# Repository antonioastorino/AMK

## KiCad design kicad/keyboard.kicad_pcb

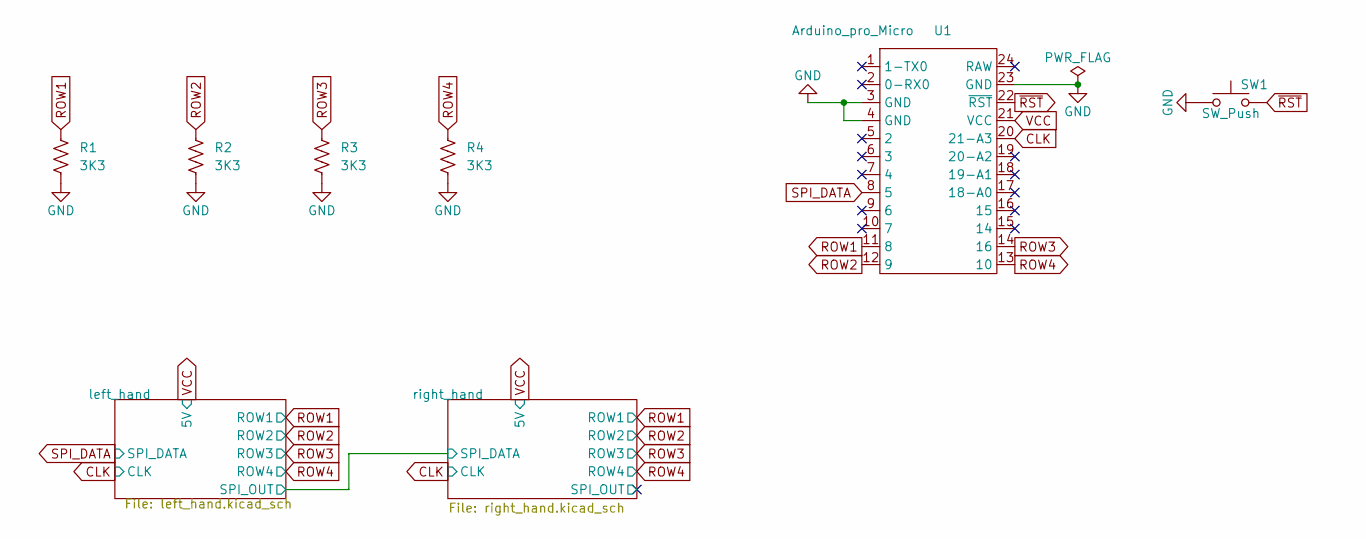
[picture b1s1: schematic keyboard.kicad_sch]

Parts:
R1, R2, R3, R4: 3K3; R_Axial_DIN0207_L6.3mm_D2.5mm_P7.62mm_Horizontal
SW1: SW_Push; DIP-2_P5.08mm
U1: Arduino_pro_Micro; DIP-24_W15.24mm

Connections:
CLK: U1.20 (21-A3); also elsewhere on the board
GND: R1.2, R2.2, R3.2, R4.2, SW1.1, U1.3 (GND), U1.4 (GND), U1.23 (GND); also elsewhere on the board
ROW1: R1.1, U1.11 (8); also elsewhere on the board
ROW2: R2.1, U1.12 (9); also elsewhere on the board
ROW3: R3.1, U1.14 (16); also elsewhere on the board
ROW4: R4.1, U1.13 (10); also elsewhere on the board
SPI_DATA: U1.8 (5); also elsewhere on the board
VCC: U1.21 (VCC); also elsewhere on the board
~RST: SW1.2, U1.22 (~RST)

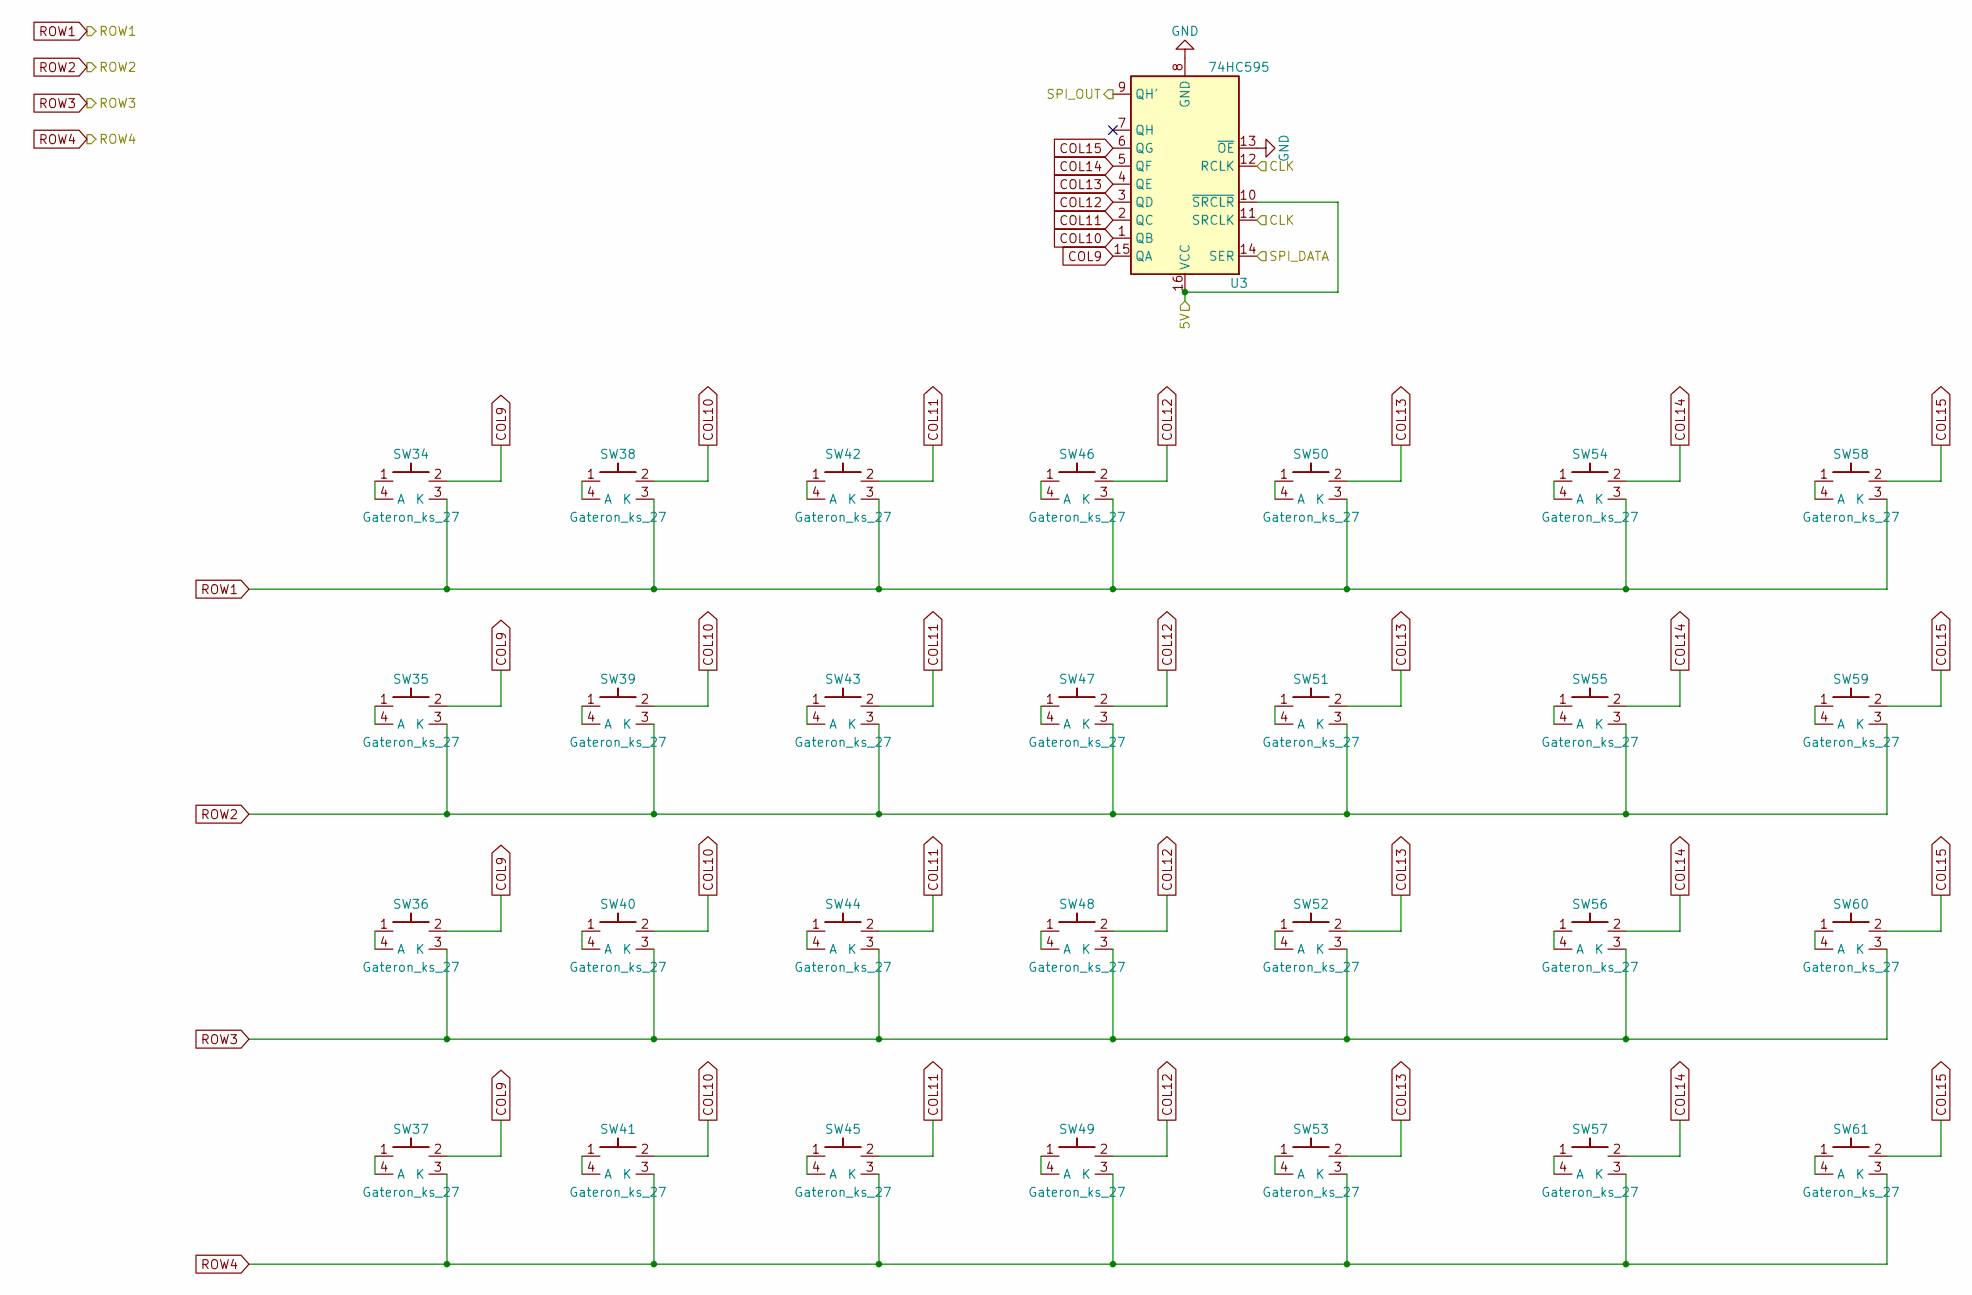
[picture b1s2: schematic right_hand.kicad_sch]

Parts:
SW34, SW35, SW36, SW37, SW38, SW39, SW40, SW41, SW42, SW43, SW44, SW45, SW46, SW47, SW48, SW49, SW50, SW51, SW52, SW53, SW54, SW55, SW56, SW57, SW58, SW59, SW60, SW61: Gateron_ks_27
U3: 74HC595; DIP-16_W7.62mm_Socket

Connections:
/left_hand/SPI_OUT: U3.14 (SER); also elsewhere on the board
/right_hand/SPI_OUT: U3.9 (QH')
CLK: U3.11 (SRCLK), U3.12 (RCLK); also elsewhere on the board
COL9: SW34.2, SW35.2, SW36.2, SW37.2, U3.15 (QA)
COL10: SW38.2, SW39.2, SW40.2, SW41.2, U3.1 (QB)
COL11: SW42.2, SW43.2, SW44.2, SW45.2, U3.2 (QC)
COL12: SW46.2, SW47.2, SW48.2, SW49.2, U3.3 (QD)
COL13: SW50.2, SW51.2, SW52.2, SW53.2, U3.4 (QE)
COL14: SW54.2, SW55.2, SW56.2, SW57.2, U3.5 (QF)
COL15: SW58.2, SW59.2, SW60.2, SW61.2, U3.6 (QG)
GND: U3.8 (GND), U3.13 (~OE); also elsewhere on the board
unnamed: SW34.1, SW34.4 (A)
unnamed: SW35.1, SW35.4 (A)
unnamed: SW36.1, SW36.4 (A)
unnamed: SW37.1, SW37.4 (A)
unnamed: SW38.1, SW38.4 (A)
unnamed: SW39.1, SW39.4 (A)
unnamed: SW40.1, SW40.4 (A)
unnamed: SW41.1, SW41.4 (A)
unnamed: SW42.1, SW42.4 (A)
unnamed: SW43.1, SW43.4 (A)
unnamed: SW44.1, SW44.4 (A)
unnamed: SW45.1, SW45.4 (A)
unnamed: SW46.1, SW46.4 (A)
unnamed: SW47.1, SW47.4 (A)
unnamed: SW48.1, SW48.4 (A)
unnamed: SW49.1, SW49.4 (A)
unnamed: SW50.1, SW50.4 (A)
unnamed: SW51.1, SW51.4 (A)
unnamed: SW52.1, SW52.4 (A)
unnamed: SW53.1, SW53.4 (A)
unnamed: SW54.1, SW54.4 (A)
unnamed: SW55.1, SW55.4 (A)
unnamed: SW56.1, SW56.4 (A)
unnamed: SW57.1, SW57.4 (A)
unnamed: SW58.1, SW58.4 (A)
unnamed: SW59.1, SW59.4 (A)
unnamed: SW60.1, SW60.4 (A)
unnamed: SW61.1, SW61.4 (A)
ROW1: SW34.3 (K), SW38.3 (K), SW42.3 (K), SW46.3 (K), SW50.3 (K), SW54.3 (K), SW58.3 (K); also elsewhere on the board
ROW2: SW35.3 (K), SW39.3 (K), SW43.3 (K), SW47.3 (K), SW51.3 (K), SW55.3 (K), SW59.3 (K); also elsewhere on the board
ROW3: SW36.3 (K), SW40.3 (K), SW44.3 (K), SW48.3 (K), SW52.3 (K), SW56.3 (K), SW60.3 (K); also elsewhere on the board
ROW4: SW37.3 (K), SW41.3 (K), SW45.3 (K), SW49.3 (K), SW53.3 (K), SW57.3 (K), SW61.3 (K); also elsewhere on the board
VCC: U3.10 (~SRCLR), U3.16 (VCC); also elsewhere on the board

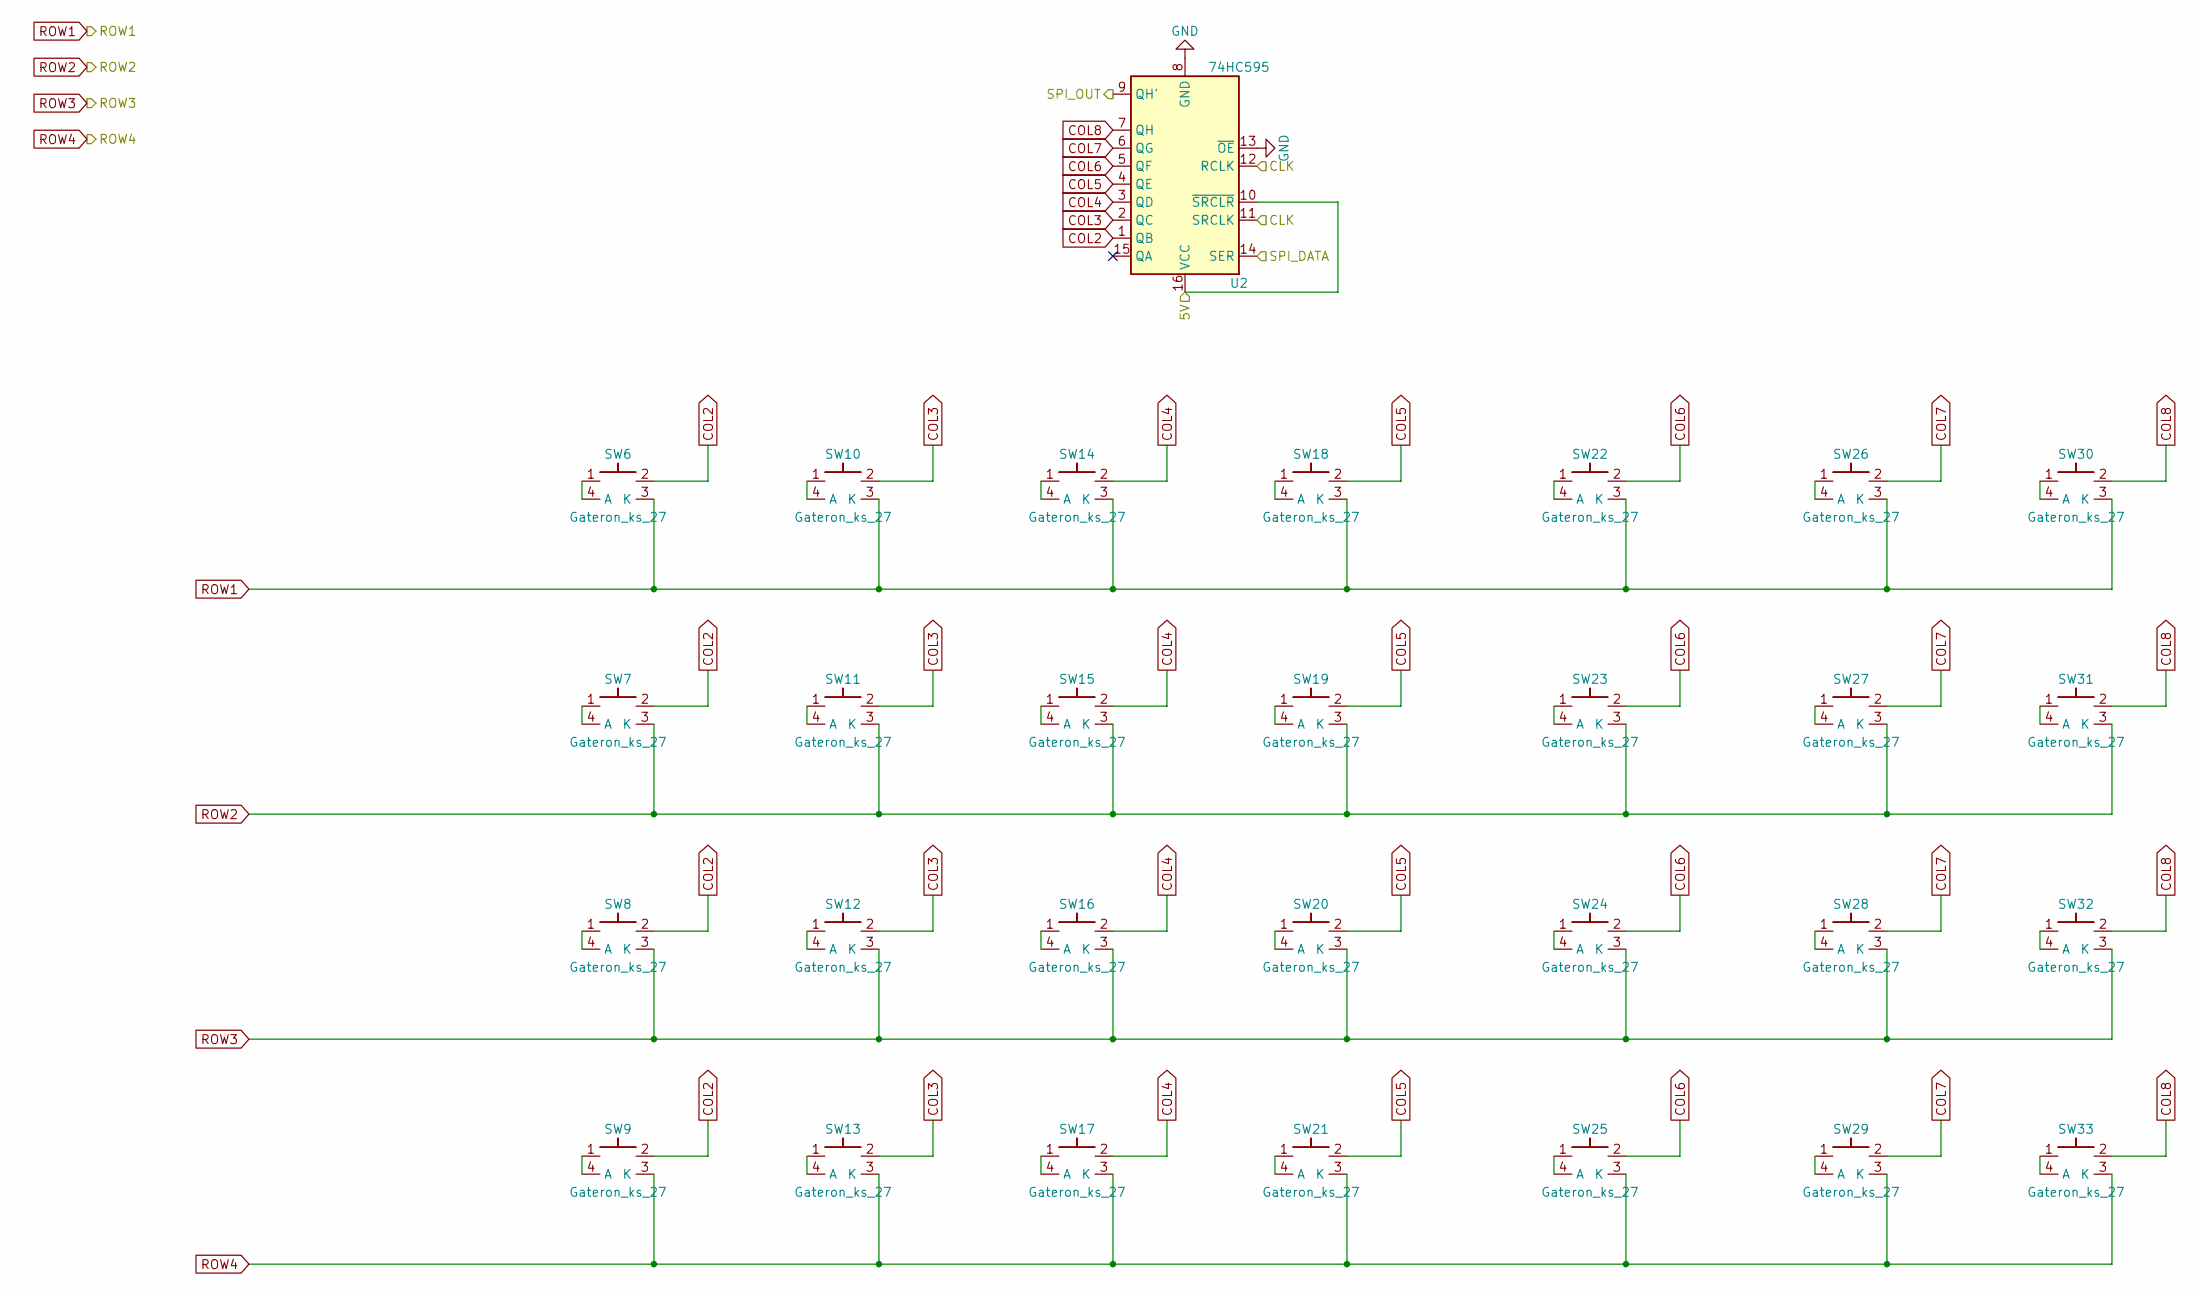
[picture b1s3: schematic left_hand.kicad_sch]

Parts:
SW6, SW7, SW8, SW9, SW10, SW11, SW12, SW13, SW14, SW15, SW16, SW17, SW18, SW19, SW20, SW21, SW22, SW23, SW24, SW25, SW26, SW27, SW28, SW29, SW30, SW31, SW32, SW33: Gateron_ks_27
U2: 74HC595; DIP-16_W7.62mm_Socket

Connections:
/left_hand/SPI_OUT: U2.9 (QH'); also elsewhere on the board
CLK: U2.11 (SRCLK), U2.12 (RCLK); also elsewhere on the board
COL2: SW6.2, SW7.2, SW8.2, SW9.2, U2.1 (QB)
COL3: SW10.2, SW11.2, SW12.2, SW13.2, U2.2 (QC)
COL4: SW14.2, SW15.2, SW16.2, SW17.2, U2.3 (QD)
COL5: SW18.2, SW19.2, SW20.2, SW21.2, U2.4 (QE)
COL6: SW22.2, SW23.2, SW24.2, SW25.2, U2.5 (QF)
COL7: SW26.2, SW27.2, SW28.2, SW29.2, U2.6 (QG)
COL8: SW30.2, SW31.2, SW32.2, SW33.2, U2.7 (QH)
GND: U2.8 (GND), U2.13 (~OE); also elsewhere on the board
unnamed: SW6.1, SW6.4 (A)
unnamed: SW7.1, SW7.4 (A)
unnamed: SW8.1, SW8.4 (A)
unnamed: SW9.1, SW9.4 (A)
unnamed: SW10.1, SW10.4 (A)
unnamed: SW11.1, SW11.4 (A)
unnamed: SW12.1, SW12.4 (A)
unnamed: SW13.1, SW13.4 (A)
unnamed: SW14.1, SW14.4 (A)
unnamed: SW15.1, SW15.4 (A)
unnamed: SW16.1, SW16.4 (A)
unnamed: SW17.1, SW17.4 (A)
unnamed: SW18.1, SW18.4 (A)
unnamed: SW19.1, SW19.4 (A)
unnamed: SW20.1, SW20.4 (A)
unnamed: SW21.1, SW21.4 (A)
unnamed: SW22.1, SW22.4 (A)
unnamed: SW23.1, SW23.4 (A)
unnamed: SW24.1, SW24.4 (A)
unnamed: SW25.1, SW25.4 (A)
unnamed: SW26.1, SW26.4 (A)
unnamed: SW27.1, SW27.4 (A)
unnamed: SW28.1, SW28.4 (A)
unnamed: SW29.1, SW29.4 (A)
unnamed: SW30.1, SW30.4 (A)
unnamed: SW31.1, SW31.4 (A)
unnamed: SW32.1, SW32.4 (A)
unnamed: SW33.1, SW33.4 (A)
ROW1: SW6.3 (K), SW10.3 (K), SW14.3 (K), SW18.3 (K), SW22.3 (K), SW26.3 (K), SW30.3 (K); also elsewhere on the board
ROW2: SW7.3 (K), SW11.3 (K), SW15.3 (K), SW19.3 (K), SW23.3 (K), SW27.3 (K), SW31.3 (K); also elsewhere on the board
ROW3: SW8.3 (K), SW12.3 (K), SW16.3 (K), SW20.3 (K), SW24.3 (K), SW28.3 (K), SW32.3 (K); also elsewhere on the board
ROW4: SW9.3 (K), SW13.3 (K), SW17.3 (K), SW21.3 (K), SW25.3 (K), SW29.3 (K), SW33.3 (K); also elsewhere on the board
SPI_DATA: U2.14 (SER); also elsewhere on the board
VCC: U2.10 (~SRCLR), U2.16 (VCC); also elsewhere on the board

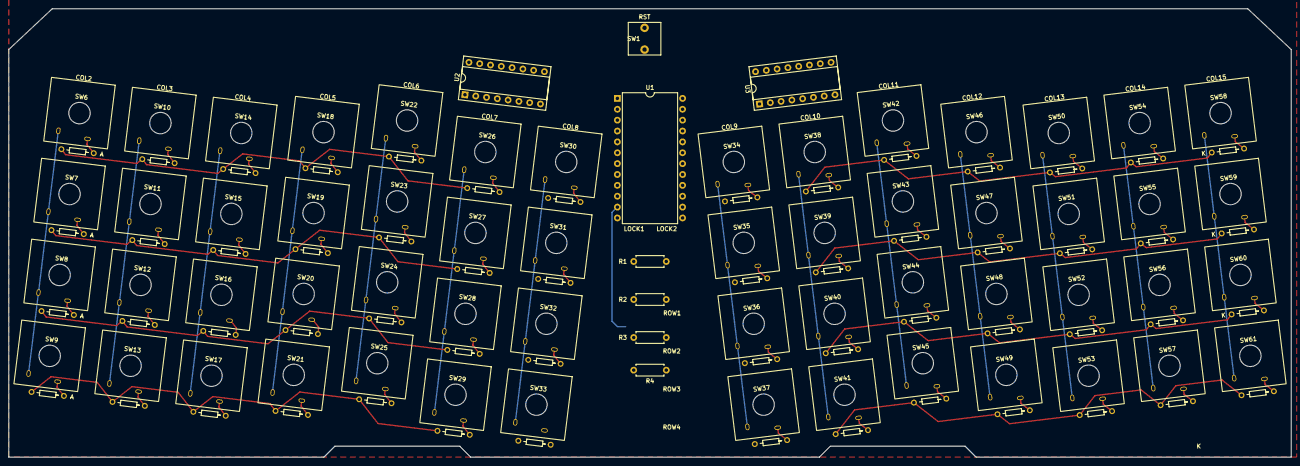
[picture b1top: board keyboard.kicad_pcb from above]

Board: 2 copper layers, 299.7 x 104.8 mm, 64 parts (0 on the bottom side), 80 nets.

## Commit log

2022-11-05 Improve layout change
2022-11-05 Add keypad keys
2022-11-05 Add LED driving
2022-11-05 Add KiCad project
2022-11-09 Write to oled and flush registers
2022-11-09 TMP: fixing RES and RST
2022-11-09 Update keyboard
2022-11-11 TMP: Add graphics with pixel
2022-11-12 Use arduino-cli
2022-11-12 Working on bitmap generator
2022-11-12 Size is an input
2022-11-12 Fix byte computation
2022-11-12 Add inline symbol
2022-11-14 Add key modifiers
2022-11-20 Custom keyboard library
2022-11-20 Update layout
2022-11-21 Remove KP for better compatibility
2022-11-21 Clear display on layer 2
2022-11-21 Rearrange layout dimensions
2022-12-13 Prevent undesired multiple keypress
2022-12-13 TMP: remove unused stuff
